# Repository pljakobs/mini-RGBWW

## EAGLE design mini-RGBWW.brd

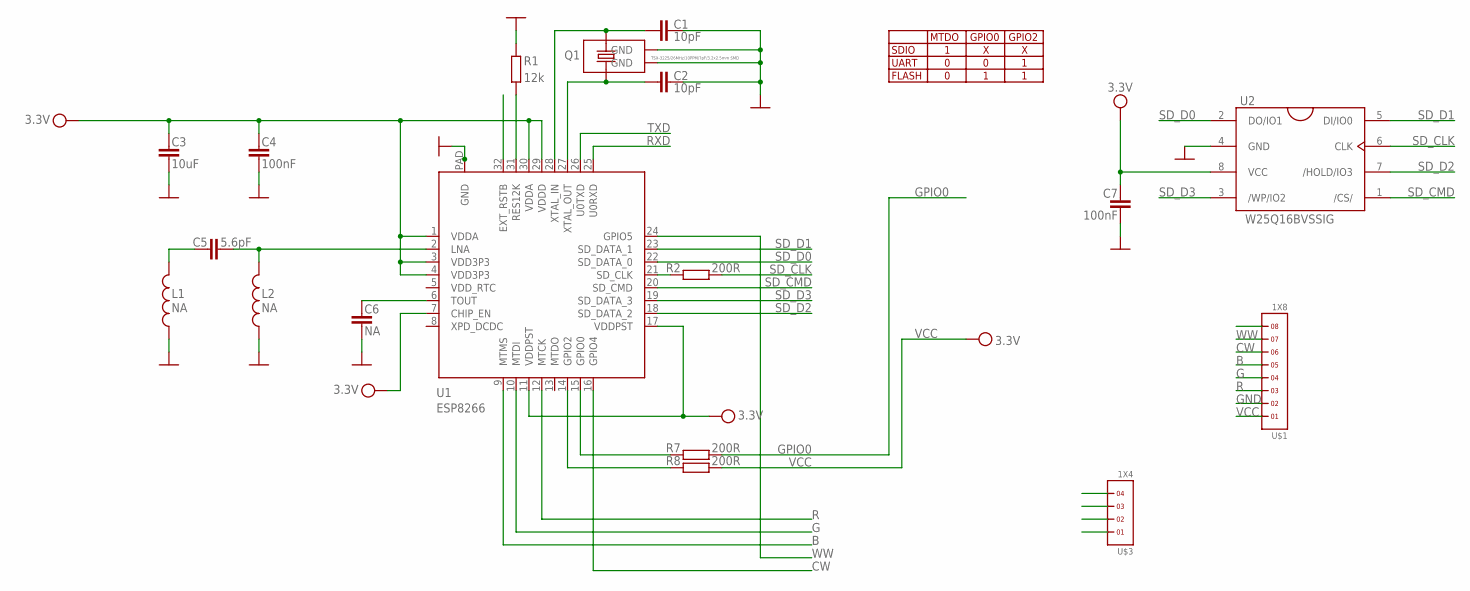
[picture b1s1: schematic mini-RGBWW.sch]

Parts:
C1, C2: 10pF; C0402_TI
C3: 10uF; C0603_DWS
C4, C7: 100nF; C0402_TI
C5: 5.6pF; C0402_TI
C6: NA; C0402_TI
L1, L2: NA; L0402_TI
Q1: TSX-3225/26MHz/10PPM/7pF/3.2x2.5mm SMD; NX3225SA
R1: 12k; R0402_TI
R2, R7, R8: 200R; R0402_TI
U1: ESP8266; QFN32_PAD
U2: W25Q16BVSSIG; SO8_ATMEL_FLASH
U$1: 1X8
U$3: 1X4

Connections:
ANT: C5.1, L1.2
B: U1.9 (MTMS), U$1.5
CW: U1.16 (GPIO4), U$1.6
G: U1.10 (MTDI), U$1.4
GND: C1.1, C2.1, C3.2, C4.2, C6.2, C7.2, L1.1, L2.1, Q1.NC_1 (GND), Q1.NC_2 (GND), R1.2, U1.P$1 (GND), U1.P$2 (GND), U1.P$3 (GND), U1.P$4 (GND), U1.P$5 (GND), U1.P$6 (GND), U1.P$7 (GND), U1.P$8 (GND), U1.P$9 (GND), U1.PAD (GND), U2.4 (GND), U$1.2
GPIO0: R7.1, U$3.1
GPIO0_: R7.2, U1.15 (GPIO0)
GPIO2_: R8.2, U1.14 (GPIO2)
LNA: C5.2, L2.2, U1.2 (LNA)
unnamed: C6.1, U1.6 (TOUT)
unnamed: R2.2, U1.21 (SD_CLK)
R: U1.12 (MTCK), U$1.3
RES12K: R1.1, U1.31 (RES12K)
RST: U1.32 (EXT_RSTB), U$3.2
RXD: U1.25 (U0RXD), U$3.3
SD_CLK: R2.1, U2.6 (CLK)
SD_CMD: U1.20 (SD_CMD), U2.1 (/CS/)
SD_D0: U1.22 (SD_DATA_0), U2.2 (DO/IO1)
SD_D1: U1.23 (SD_DATA_1), U2.5 (DI/IO0)
SD_D2: U1.18 (SD_DATA_2), U2.7 (/HOLD/IO3)
SD_D3: U1.19 (SD_DATA_3), U2.3 (/WP/IO2)
TXD: U1.26 (U0TXD), U$3.4
VCC: C3.1, C4.1, C7.1, R8.1, U1.1 (VDDA), U1.3 (VDD3P3), U1.4 (VDD3P3), U1.7 (CHIP_EN), U1.11 (VDDPST), U1.17 (VDDPST), U1.29 (VDDD), U1.30 (VDDA), U2.8 (VCC), U$1.1
WW: U1.24 (GPIO5), U$1.7
XTAL_IN: C1.2, Q1.1, U1.28 (XTAL_IN)
XTAL_OUT: C2.2, Q1.2, U1.27 (XTAL_OUT)

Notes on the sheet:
SDIO
UART
FLASH
MTDO
GPIO0
GPIO2

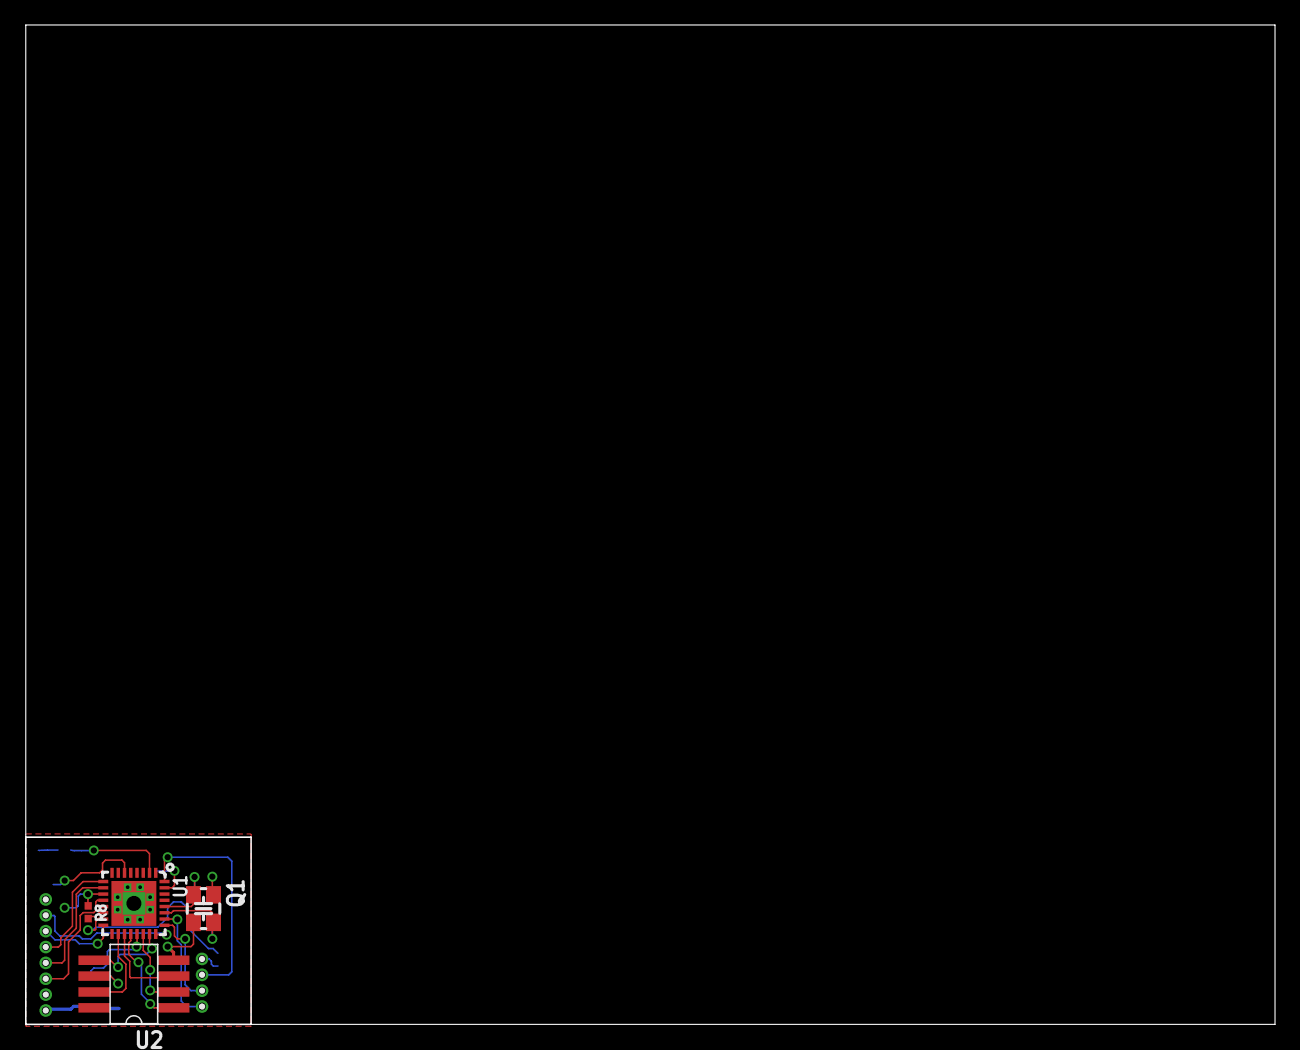
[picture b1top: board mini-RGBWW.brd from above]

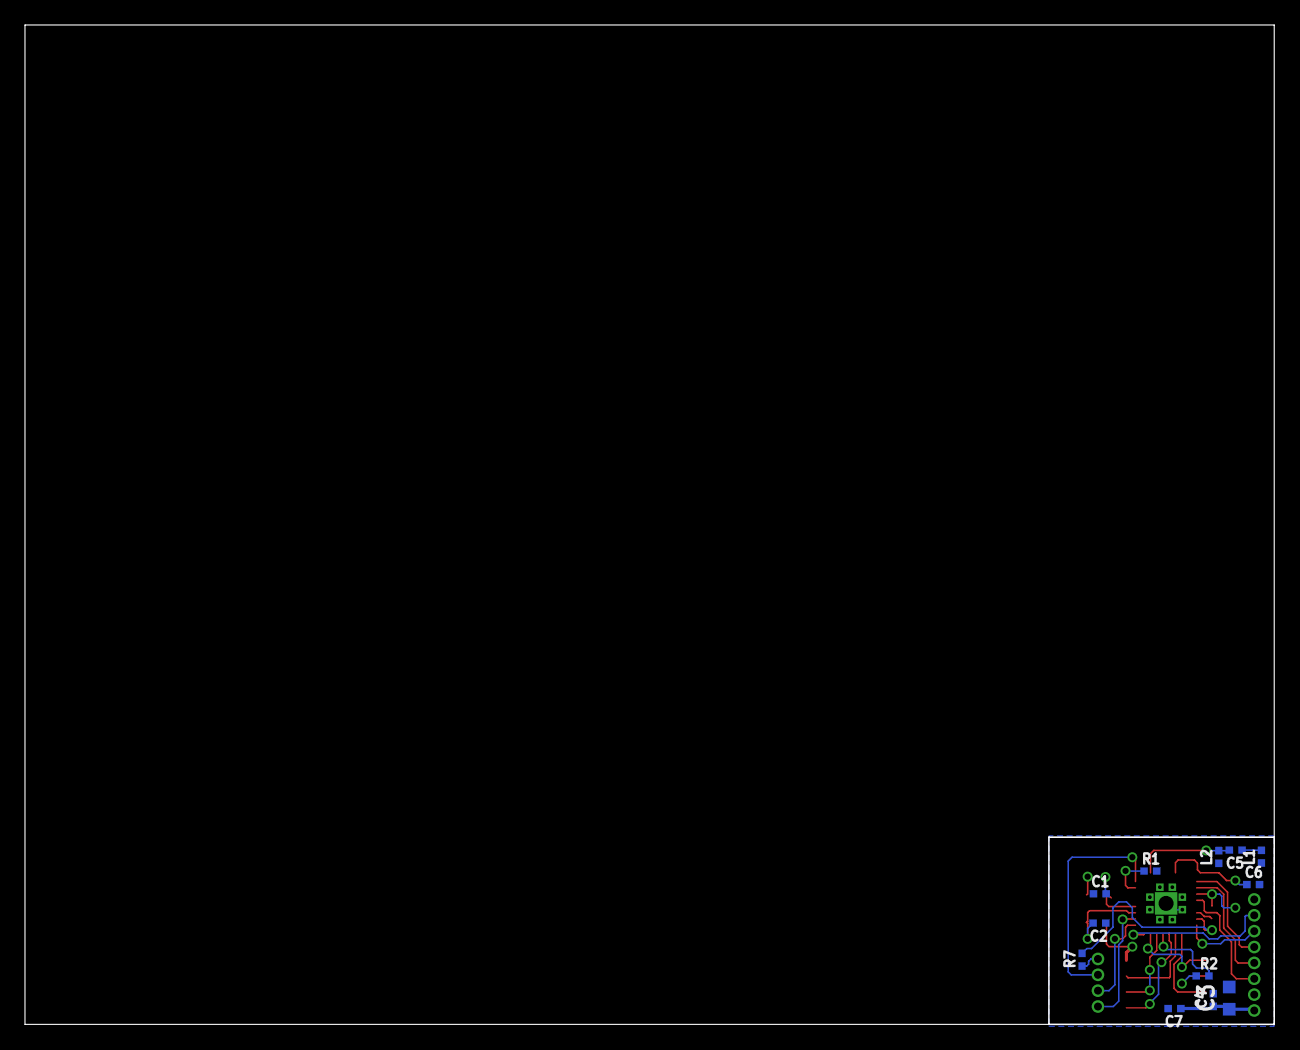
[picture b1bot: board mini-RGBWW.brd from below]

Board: 2 copper layers, 99.9 x 79.9 mm, 18 parts (12 on the bottom side), 26 nets.
